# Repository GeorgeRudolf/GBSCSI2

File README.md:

# GBSCSI2
Affordable SCSI Disk Emulator - upgrade over the original GBSCSI

NOTE: Above all, these boards were initially designed as a hack to satisfy my own personal needs. With that said, they've been tested fairly extensively. Please read this entire README.

Herein are the design files for all variants of GBSCSI2 in KiCad 7 format, being migrated to KiCad 9. The hardware in this repository is licensed CERN OHL-S V2, the full terms of which can be found at https://ohwr.org/cern_ohl_s_v2.pdf and https://ohwr.org/cern_ohl_s_v2.txt.

With thanks to [The Decromancer](https://decromancer.ca/) for sponsoring this project; wohali, tr0n, compu85, sabur and luigi30 for testing; and the rest of UHF for their continued enthusiasm and support. Also to [Rabbit Hole Computing](https://www.rabbitholecomputing.com/) for their continued maintenance of the ZuluSCSI firmware that makes these boards complete, and further testing and collaboration on this project.

# HOW TO:
1. Buy board from decromancer or [Emmy Bear Retro](https://retro.emmybear.shop)
2. It arrives at your doorstep ready to use

OR

1. Get assembled boards using the files in this repository
2. Solder header of your choice
3. (Except for RP2040 version, or if ordering Pico from JLC) Solder RPi Pico - use Pico-W if you want DaynaPORT capabilities for a Mac
4. Go to https://github.com/ZuluSCSI/ZuluSCSI-firmware and grab the Pico/Pico_DaynaPORT version of the latest release and flash to the board by connecting via USB while holding BOOTSEL (or toggling the boot dip switch for RP2040)

# The (very important) details:

1. GBSCSI2 is being moved to a revised hierarchical design that allows for modularity and ease of customization, while maintaining uniformity. The whole project is considered WIP - this warning will be removed once things are tested. Previous versions have been moved to an archive folder. More about them below.

2. The archived Wide SCSI variants are BROKEN. They're incomplete and not usable. 
Rabbit Hole Computing has forked these designs, corrected their flaws and finished the implementation in a manner compatible with standard ZuluSCSI firmware. This fork is now available at https://github.com/ZuluSCSI/ZuluSCSI-Ultra-Wide-OSHW-RP2350B.

3. The variants tagged "untested" are exactly that. I've never personally made boards from them. Use at your own risk.

4. For changes and errata, see the relevant files in the repo.

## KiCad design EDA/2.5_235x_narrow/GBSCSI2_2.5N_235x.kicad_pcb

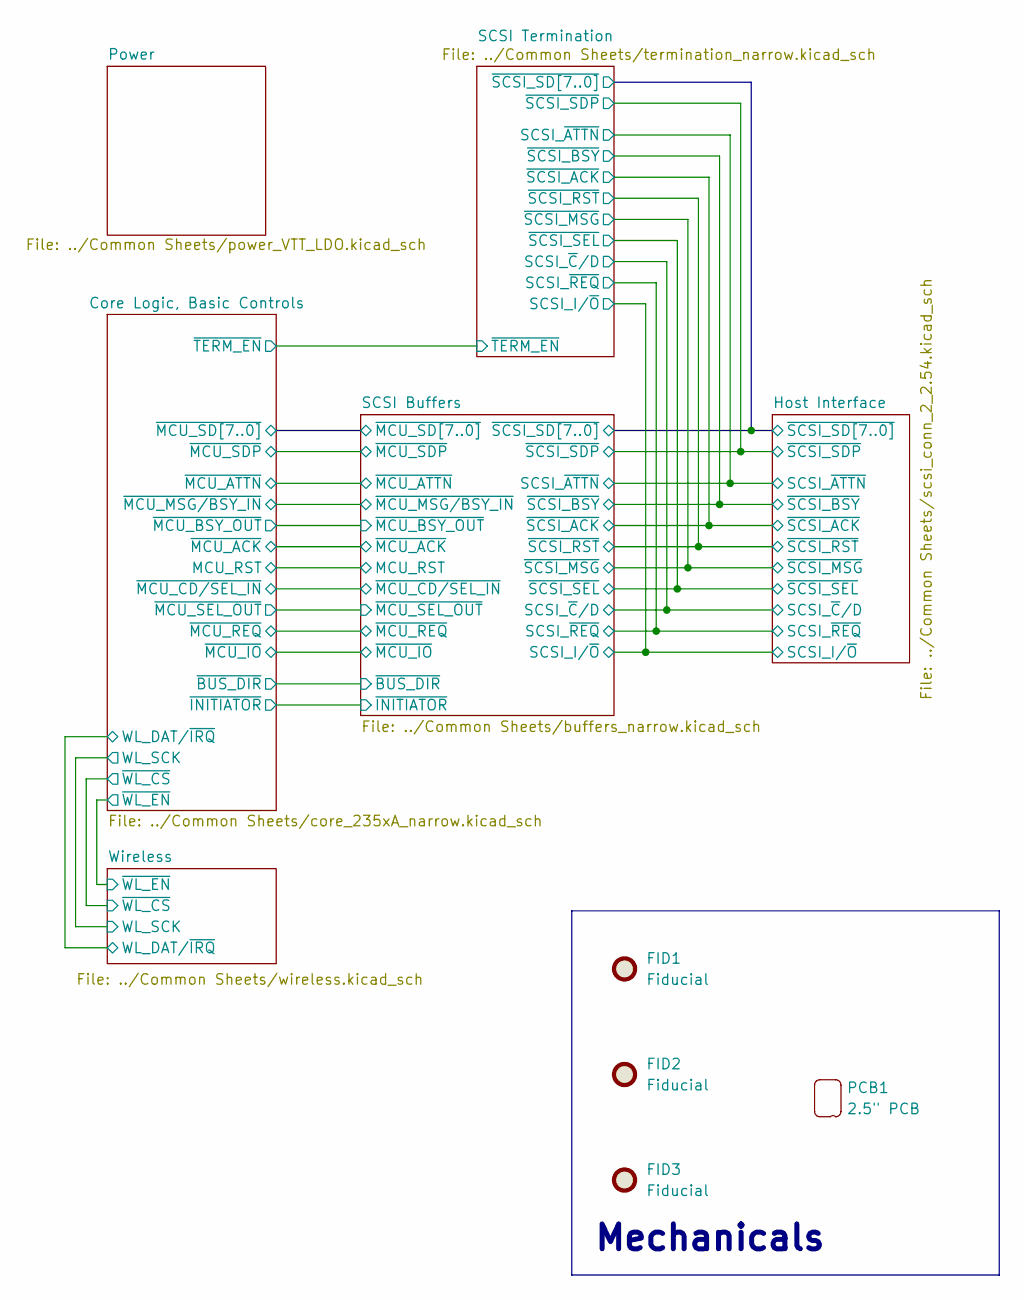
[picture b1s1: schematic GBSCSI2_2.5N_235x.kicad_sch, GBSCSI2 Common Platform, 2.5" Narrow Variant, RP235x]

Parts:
FID1, FID2, FID3: Fiducial; Fiducial_0.5mm_Mask1mm; LCSC N/A
PCB1: 2.5" PCB; GBSCSI2_2.5_PCB

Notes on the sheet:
Mechanicals

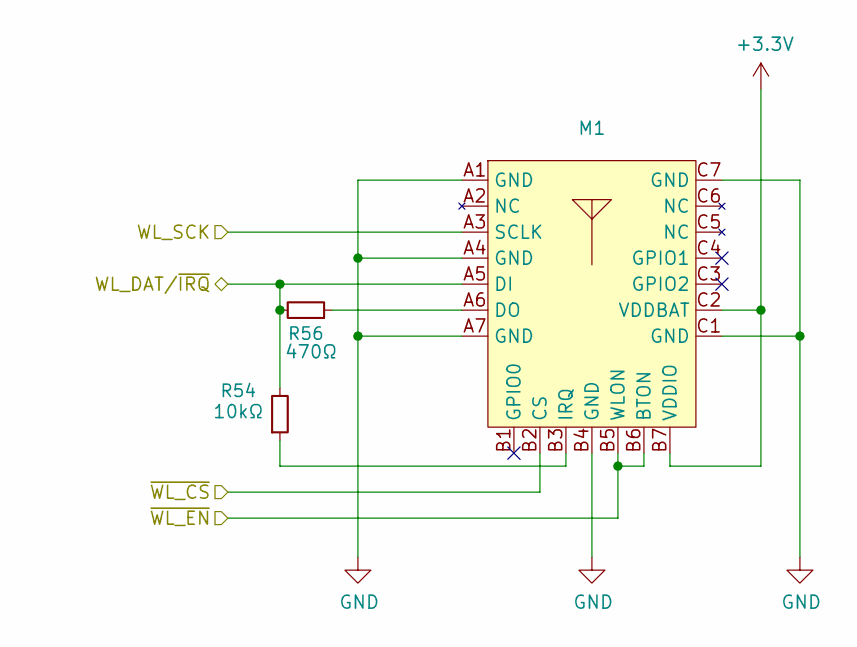
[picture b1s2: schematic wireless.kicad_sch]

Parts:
M1: RPi_RM2; LCSC N/A
R54: 10kΩ; R_0402_1005Metric; LCSC C25744
R56: 470Ω; R_0402_1005Metric

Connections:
+3.3V: M1.B7 (VDDIO), M1.C2 (VDDBAT); also elsewhere on the board
/Core Logic, Basic Controls/WL_DAT/~IRQ: M1.A5 (DI), R54.2, R56.2; also elsewhere on the board
/Core Logic, Basic Controls/WL_SCK: M1.A3 (SCLK); also elsewhere on the board
/Core Logic, Basic Controls/~WL_CS: M1.B2 (CS); also elsewhere on the board
/Core Logic, Basic Controls/~WL_EN: M1.B5 (WLON), M1.B6 (BTON); also elsewhere on the board
GND: M1.A1 (GND), M1.A4 (GND), M1.A7 (GND), M1.B4 (GND), M1.C1 (GND), M1.C7 (GND); also elsewhere on the board
unnamed: M1.A6 (DO), R56.1
unnamed: M1.B3 (IRQ), R54.1

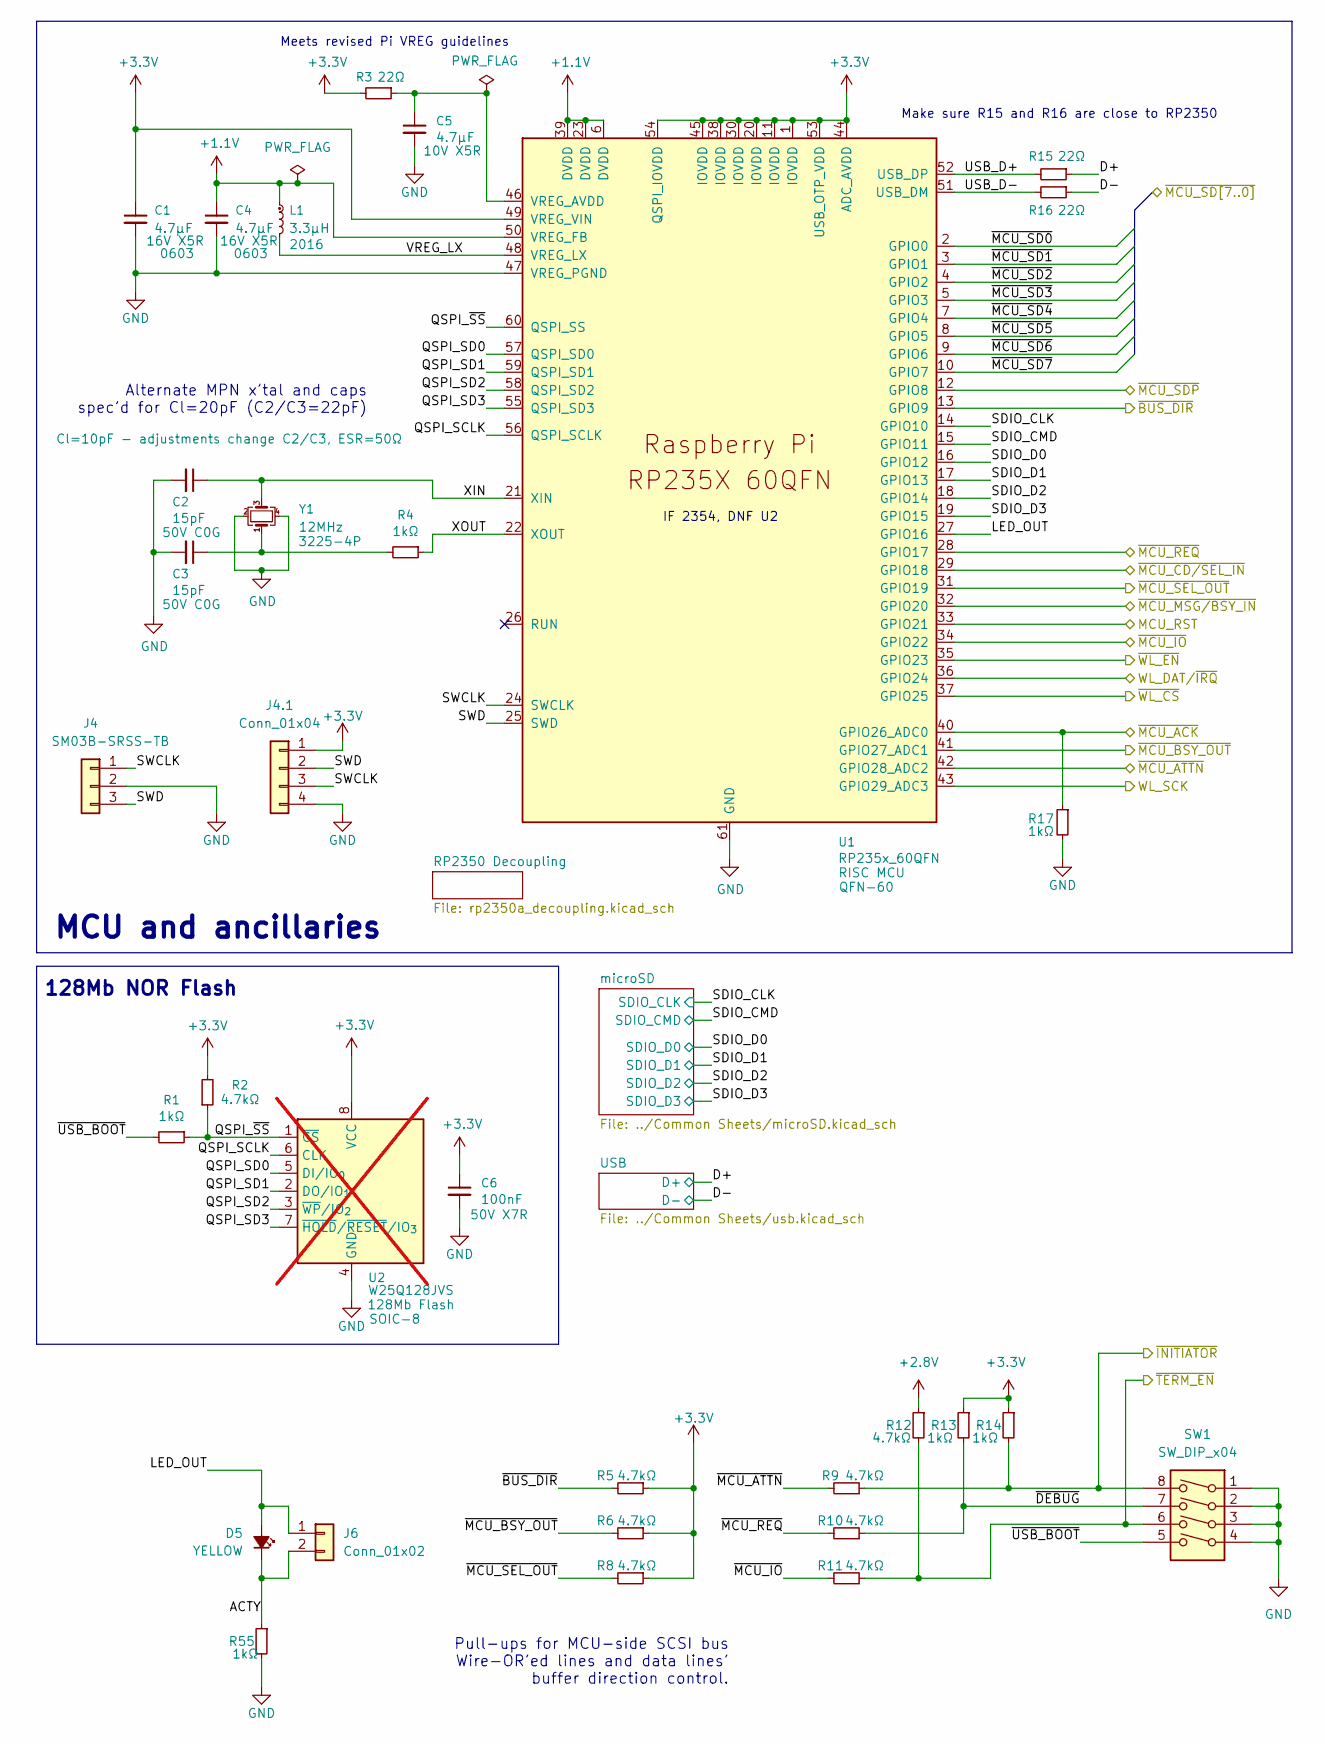
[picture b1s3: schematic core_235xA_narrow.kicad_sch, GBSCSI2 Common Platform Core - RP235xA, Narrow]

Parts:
C1, C4: 4.7μF; C_0603_1608Metric; LCSC C19666
C2, C3: 15pF; C_0402_1005Metric; LCSC C1548
C5: 4.7μF; C_0402_1005Metric; LCSC C23733
C6: 100nF; C_0402_1005Metric; LCSC C307331
D5: YELLOW; LED_0603_1608Metric; LCSC C72038
J4: SM03B-SRSS-TB; JST_SH_SM03B-SRSS-TB_1x03-1MP_P1.00mm_Horizontal; LCSC C160403
J4.1: Conn_01x04; PinHeader_1x04_P2.54mm_Vertical; LCSC N/A
J6: Conn_01x02; PinHeader_1x02_P2.54mm_Vertical; LCSC N/A
L1: 3.3μH; L_Abracon_AOTA-B2016; LCSC C42411119
R1, R4: 1kΩ; R_0402_1005Metric; LCSC C11702
R2: 4.7kΩ; R_0402_1005Metric; LCSC C25900
R3, R15, R16: 22Ω; R_0402_1005Metric; LCSC C25092
R5, R6, R8, R9, R10, R11, R12: 4.7kΩ; R_0603_1608Metric; LCSC C23162
R13, R14, R17, R55: 1kΩ; R_0603_1608Metric; LCSC C21190
SW1: SW_DIP_x04; SW_DIP_SPSTx04_Slide_6.7x11.72mm_W8.61mm_P2.54mm_LowProfile; LCSC C5160841
U1: RP235x_60QFN; RP2350-QFN-60-1EP_7x7_P0.4mm_EP3.4x3.4mm_ThermalVias; LCSC C41378174
U2: W25Q128JVS; SOIC-8_5.3x5.3mm_P1.27mm; LCSC C97521; not fitted
Y1: 12MHz; Crystal_SMD_3225-4Pin_3.2x2.5mm; LCSC C20625731

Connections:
+1.1V: C4.1, L1.1, U1.6 (DVDD), U1.23 (DVDD), U1.39 (DVDD), U1.50 (VREG_FB); also elsewhere on the board
+2.8V: R12.1; also elsewhere on the board
+3.3V: C1.1, C6.1, J4.1.1, R2.2, R3.2, R5.1, R6.1, R8.1, R13.1, R14.1, U1.1 (IOVDD), U1.11 (IOVDD), U1.20 (IOVDD), U1.30 (IOVDD), U1.38 (IOVDD), U1.44 (ADC_AVDD), U1.45 (IOVDD), U1.49 (VREG_VIN), U1.53 (USB_OTP_VDD), U1.54 (QSPI_IOVDD), U2.8 (VCC); also elsewhere on the board
/Core Logic, Basic Controls/ACTY: D5.1 (K), J6.2, R55.1
/Core Logic, Basic Controls/D+: R15.1; also elsewhere on the board
/Core Logic, Basic Controls/D-: R16.1; also elsewhere on the board
/Core Logic, Basic Controls/LED_OUT: D5.2 (A), J6.1, U1.27 (GPIO16)
/Core Logic, Basic Controls/MCU_RST: U1.33 (GPIO21); also elsewhere on the board
/Core Logic, Basic Controls/QSPI_SCLK: U1.56 (QSPI_SCLK), U2.6 (CLK)
/Core Logic, Basic Controls/QSPI_SD0: U1.57 (QSPI_SD0), U2.5 (DI/IO_{0})
/Core Logic, Basic Controls/QSPI_SD1: U1.59 (QSPI_SD1), U2.2 (DO/IO_{1})
/Core Logic, Basic Controls/QSPI_SD2: U1.58 (QSPI_SD2), U2.3 (~WP/IO_{2})
/Core Logic, Basic Controls/QSPI_SD3: U1.55 (QSPI_SD3), U2.7 (~HOLD/~RESET/IO_{3})
/Core Logic, Basic Controls/QSPI_~SS: R1.1, R2.1, U1.60 (QSPI_SS), U2.1 (~CS)
/Core Logic, Basic Controls/SDIO_CLK: U1.14 (GPIO10); also elsewhere on the board
/Core Logic, Basic Controls/SDIO_CMD: U1.15 (GPIO11); also elsewhere on the board
/Core Logic, Basic Controls/SDIO_D0: U1.16 (GPIO12); also elsewhere on the board
/Core Logic, Basic Controls/SDIO_D1: U1.17 (GPIO13); also elsewhere on the board
/Core Logic, Basic Controls/SDIO_D2: U1.18 (GPIO14); also elsewhere on the board
/Core Logic, Basic Controls/SDIO_D3: U1.19 (GPIO15); also elsewhere on the board
/Core Logic, Basic Controls/SWCLK: J4.1, J4.1.3, U1.24 (SWCLK)
/Core Logic, Basic Controls/SWD: J4.3, J4.1.2, U1.25 (SWD)
/Core Logic, Basic Controls/USB_D+: R15.2, U1.52 (USB_DP)
/Core Logic, Basic Controls/USB_D-: R16.2, U1.51 (USB_DM)
/Core Logic, Basic Controls/VREG_LX: L1.2, U1.48 (VREG_LX)
/Core Logic, Basic Controls/WL_DAT/~IRQ: U1.36 (GPIO24); also elsewhere on the board
/Core Logic, Basic Controls/WL_SCK: U1.43 (GPIO29_ADC3); also elsewhere on the board
/Core Logic, Basic Controls/XIN: C2.1, U1.21 (XIN), Y1.3
/Core Logic, Basic Controls/XOUT: R4.1, U1.22 (XOUT)
/Core Logic, Basic Controls/~BUS_DIR: R5.2, U1.13 (GPIO9); also elsewhere on the board
/Core Logic, Basic Controls/~DEBUG: R10.1, R13.2, SW1.7
/Core Logic, Basic Controls/~INITIATOR: R9.1, R14.2, SW1.8; also elsewhere on the board
/Core Logic, Basic Controls/~MCU_ACK: R17.1, U1.40 (GPIO26_ADC0); also elsewhere on the board
/Core Logic, Basic Controls/~MCU_ATTN: R9.2, U1.42 (GPIO28_ADC2); also elsewhere on the board
/Core Logic, Basic Controls/~MCU_BSY_OUT: R6.2, U1.41 (GPIO27_ADC1); also elsewhere on the board
/Core Logic, Basic Controls/~MCU_CD/SEL_IN: U1.29 (GPIO18); also elsewhere on the board
/Core Logic, Basic Controls/~MCU_IO: R11.2, U1.34 (GPIO22); also elsewhere on the board
/Core Logic, Basic Controls/~MCU_MSG/BSY_IN: U1.32 (GPIO20); also elsewhere on the board
/Core Logic, Basic Controls/~MCU_REQ: R10.2, U1.28 (GPIO17); also elsewhere on the board
/Core Logic, Basic Controls/~MCU_SD0: U1.2 (GPIO0); also elsewhere on the board
/Core Logic, Basic Controls/~MCU_SD1: U1.3 (GPIO1); also elsewhere on the board
/Core Logic, Basic Controls/~MCU_SD2: U1.4 (GPIO2); also elsewhere on the board
/Core Logic, Basic Controls/~MCU_SD3: U1.5 (GPIO3); also elsewhere on the board
/Core Logic, Basic Controls/~MCU_SD4: U1.7 (GPIO4); also elsewhere on the board
/Core Logic, Basic Controls/~MCU_SD5: U1.8 (GPIO5); also elsewhere on the board
/Core Logic, Basic Controls/~MCU_SD6: U1.9 (GPIO6); also elsewhere on the board
/Core Logic, Basic Controls/~MCU_SD7: U1.10 (GPIO7); also elsewhere on the board
/Core Logic, Basic Controls/~MCU_SDP: U1.12 (GPIO8); also elsewhere on the board
/Core Logic, Basic Controls/~MCU_SEL_OUT: R8.2, U1.31 (GPIO19); also elsewhere on the board
/Core Logic, Basic Controls/~TERM_EN: R11.1, R12.2, SW1.6; also elsewhere on the board
/Core Logic, Basic Controls/~USB_BOOT: R1.2, SW1.5
/Core Logic, Basic Controls/~WL_CS: U1.37 (GPIO25); also elsewhere on the board
/Core Logic, Basic Controls/~WL_EN: U1.35 (GPIO23); also elsewhere on the board
GND: C1.2, C2.2, C3.2, C4.2, C5.2, C6.2, J4.2, J4.1.4, R17.2, R55.2, SW1.1, SW1.2, SW1.3, SW1.4, U1.47 (VREG_PGND), U1.61 (GND), U2.4 (GND), Y1.2, Y1.4; also elsewhere on the board
unnamed: C3.1, R4.2, Y1.1
unnamed: C5.1, R3.1, U1.46 (VREG_AVDD)

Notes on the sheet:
128Mb NOR Flash
Alternate MPN x'tal and caps spec'd for Cl=20pF (C2/C3=22pF)
Pull-ups for MCU-side SCSI bus Wire-OR'ed lines and data lines' buffer direction control.
IF 2354, DNF U2
MCU and ancillaries
Make sure R15 and R16 are close to RP2350
Meets revised Pi VREG guidelines

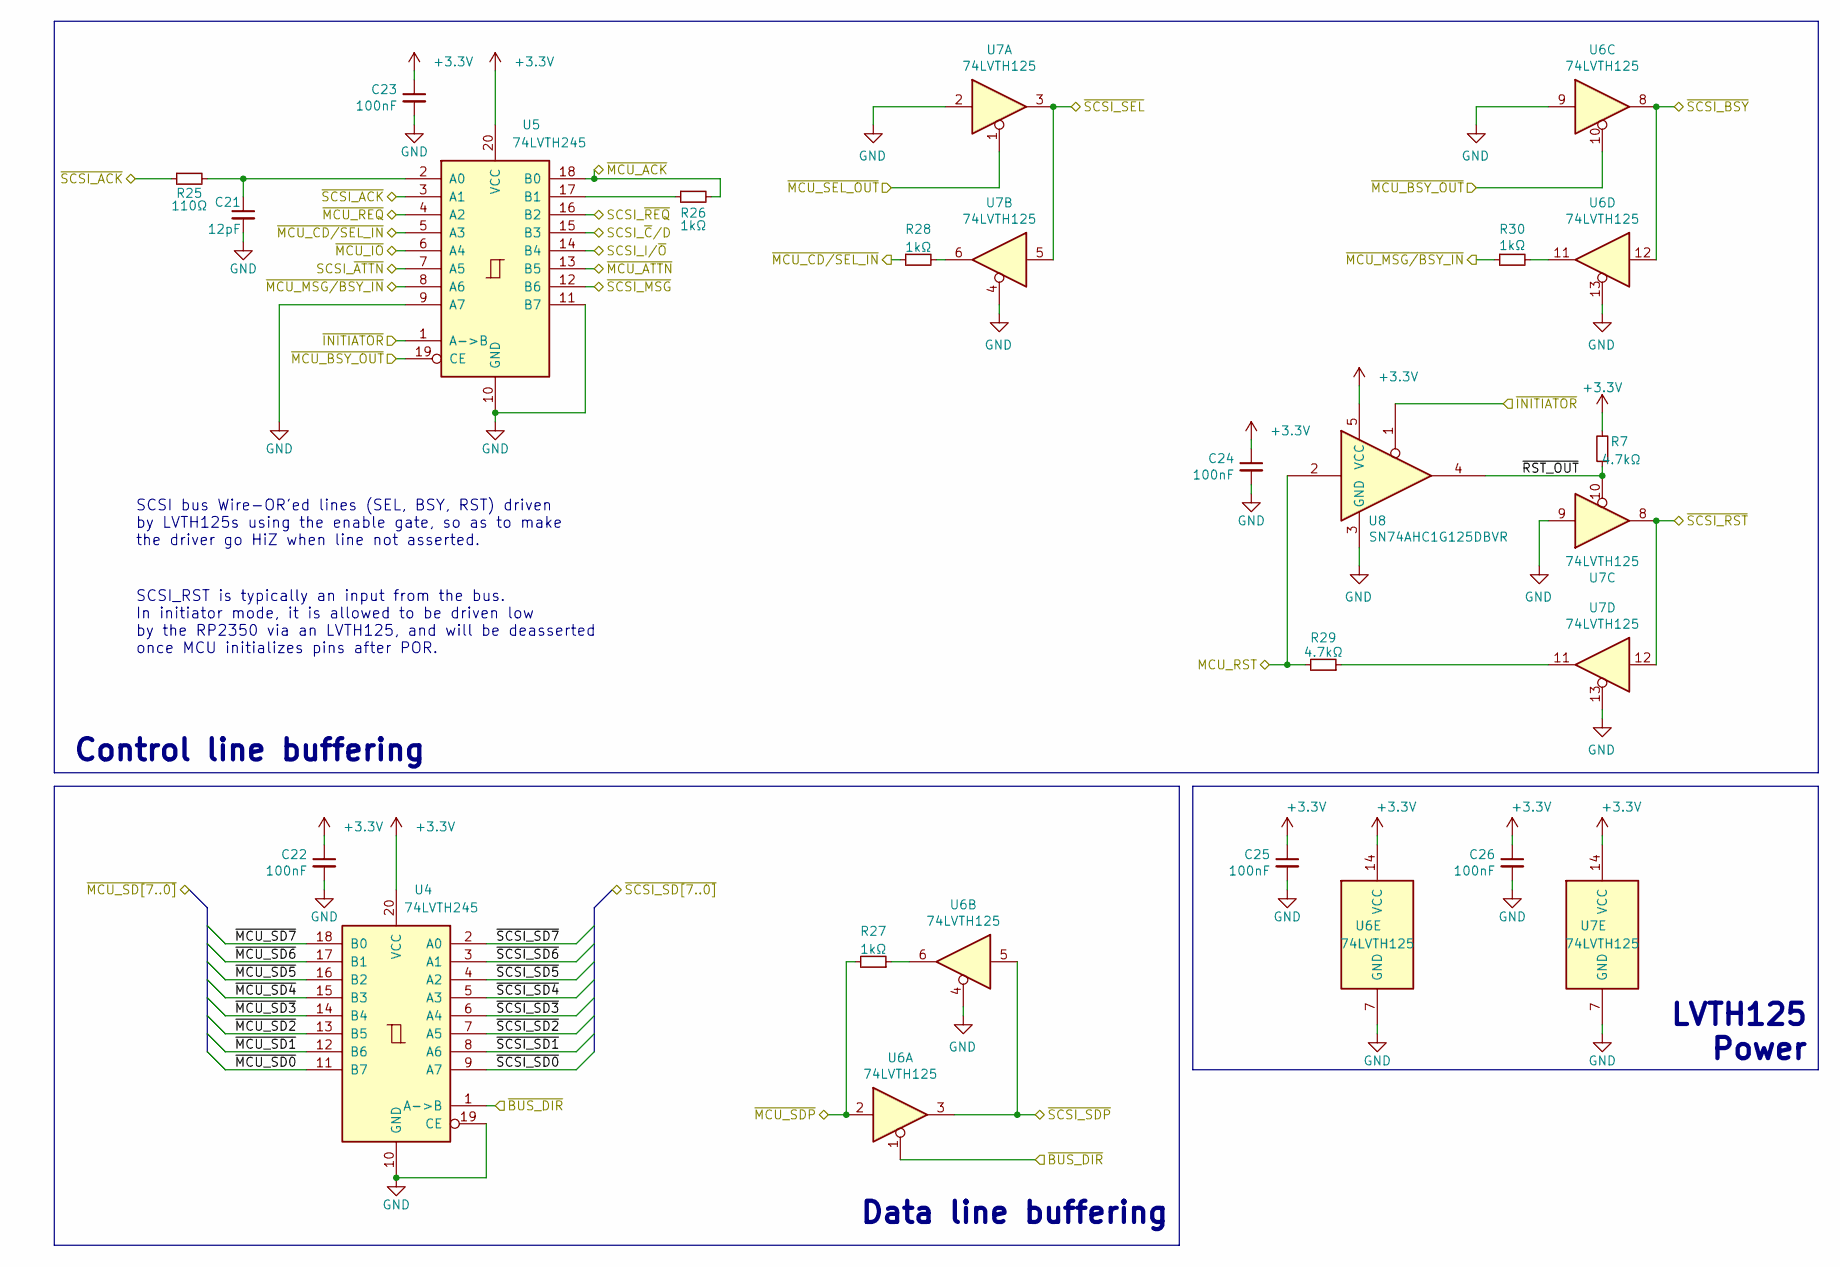
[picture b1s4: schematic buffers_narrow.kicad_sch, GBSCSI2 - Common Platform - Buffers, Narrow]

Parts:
C21: 12pF; C_0603_1608Metric; LCSC C38523
C22, C23, C24, C25, C26: 100nF; C_0603_1608Metric; LCSC C14663
R7, R29: 4.7kΩ; R_0603_1608Metric; LCSC C23162
R25: 110Ω; R_0603_1608Metric; LCSC C22781
R26, R27, R28, R30: 1kΩ; R_0603_1608Metric; LCSC C21190
U4, U5: 74LVTH245; SSOP-20_5.3x7.2mm_P0.65mm; LCSC C2652121
U6, U7: 74LVTH125; TSSOP-14_4.4x5mm_P0.65mm; LCSC C7042
U8: SN74AHC1G125DBVR; SOT-23-5; LCSC C7468

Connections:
+3.3V: C22.1, C23.1, C24.1, C25.1, C26.1, R7.2, U4.20 (VCC), U5.20 (VCC), U6.14 (VCC), U7.14 (VCC), U8.5 (VCC); also elsewhere on the board
/Core Logic, Basic Controls/MCU_RST: R29.2, U8.2; also elsewhere on the board
/Core Logic, Basic Controls/~BUS_DIR: U4.1 (A->B), U6.1; also elsewhere on the board
/Core Logic, Basic Controls/~INITIATOR: U5.1 (A->B), U8.1; also elsewhere on the board
/Core Logic, Basic Controls/~MCU_ACK: R26.2, U5.18 (B0); also elsewhere on the board
/Core Logic, Basic Controls/~MCU_ATTN: U5.13 (B5); also elsewhere on the board
/Core Logic, Basic Controls/~MCU_BSY_OUT: U5.19 (CE), U6.10; also elsewhere on the board
/Core Logic, Basic Controls/~MCU_CD/SEL_IN: R28.1, U5.5 (A3); also elsewhere on the board
/Core Logic, Basic Controls/~MCU_IO: U5.6 (A4); also elsewhere on the board
/Core Logic, Basic Controls/~MCU_MSG/BSY_IN: R30.1, U5.8 (A6); also elsewhere on the board
/Core Logic, Basic Controls/~MCU_REQ: U5.4 (A2); also elsewhere on the board
/Core Logic, Basic Controls/~MCU_SD0: U4.11 (B7); also elsewhere on the board
/Core Logic, Basic Controls/~MCU_SD1: U4.12 (B6); also elsewhere on the board
/Core Logic, Basic Controls/~MCU_SD2: U4.13 (B5); also elsewhere on the board
/Core Logic, Basic Controls/~MCU_SD3: U4.14 (B4); also elsewhere on the board
/Core Logic, Basic Controls/~MCU_SD4: U4.15 (B3); also elsewhere on the board
/Core Logic, Basic Controls/~MCU_SD5: U4.16 (B2); also elsewhere on the board
/Core Logic, Basic Controls/~MCU_SD6: U4.17 (B1); also elsewhere on the board
/Core Logic, Basic Controls/~MCU_SD7: U4.18 (B0); also elsewhere on the board
/Core Logic, Basic Controls/~MCU_SDP: R27.2, U6.2; also elsewhere on the board
/Core Logic, Basic Controls/~MCU_SEL_OUT: U7.1; also elsewhere on the board
/Host Interface/SCSI_I/~O: U5.14 (B4); also elsewhere on the board
/Host Interface/SCSI_~ATTN: U5.7 (A5); also elsewhere on the board
/Host Interface/SCSI_~C/D: U5.15 (B3); also elsewhere on the board
/Host Interface/SCSI_~REQ: U5.16 (B2); also elsewhere on the board
/Host Interface/~SCSI_ACK: R25.1, U5.3 (A1); also elsewhere on the board
/Host Interface/~SCSI_BSY: U6.8, U6.12; also elsewhere on the board
/Host Interface/~SCSI_MSG: U5.12 (B6); also elsewhere on the board
/Host Interface/~SCSI_RST: U7.8, U7.12; also elsewhere on the board
/Host Interface/~SCSI_SD0: U4.9 (A7); also elsewhere on the board
/Host Interface/~SCSI_SD1: U4.8 (A6); also elsewhere on the board
/Host Interface/~SCSI_SD2: U4.7 (A5); also elsewhere on the board
/Host Interface/~SCSI_SD3: U4.6 (A4); also elsewhere on the board
/Host Interface/~SCSI_SD4: U4.5 (A3); also elsewhere on the board
/Host Interface/~SCSI_SD5: U4.4 (A2); also elsewhere on the board
/Host Interface/~SCSI_SD6: U4.3 (A1); also elsewhere on the board
/Host Interface/~SCSI_SD7: U4.2 (A0); also elsewhere on the board
/Host Interface/~SCSI_SDP: U6.3, U6.5; also elsewhere on the board
/Host Interface/~SCSI_SEL: U7.3, U7.5; also elsewhere on the board
/SCSI Buffers/~RST_OUT: R7.1, U7.10, U8.4
GND: C21.2, C22.2, C23.2, C24.2, C25.2, C26.2, U4.10 (GND), U4.19 (CE), U5.9 (A7), U5.10 (GND), U5.11 (B7), U6.4, U6.7 (GND), U6.9, U6.13, U7.2, U7.4, U7.7 (GND), U7.9, U7.13, U8.3 (GND); also elsewhere on the board
unnamed: R27.1, U6.6
unnamed: R28.2, U7.6
unnamed: R29.1, U7.11
unnamed: R30.2, U6.11
unnamed: C21.1, R25.2, U5.2 (A0)
unnamed: R26.1, U5.17 (B1)

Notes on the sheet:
Control line buffering
SCSI_RST is typically an input from the bus. In initiator mode, it is allowed to be driven low by the RP2350 via an LVTH125, and will be deasserted once MCU initializes pins after POR.
LVTH125 Power
SCSI bus Wire-OR'ed lines (SEL, BSY, RST) driven by LVTH125s using the enable gate, so as to make the driver go HiZ when line not asserted.
Data line buffering

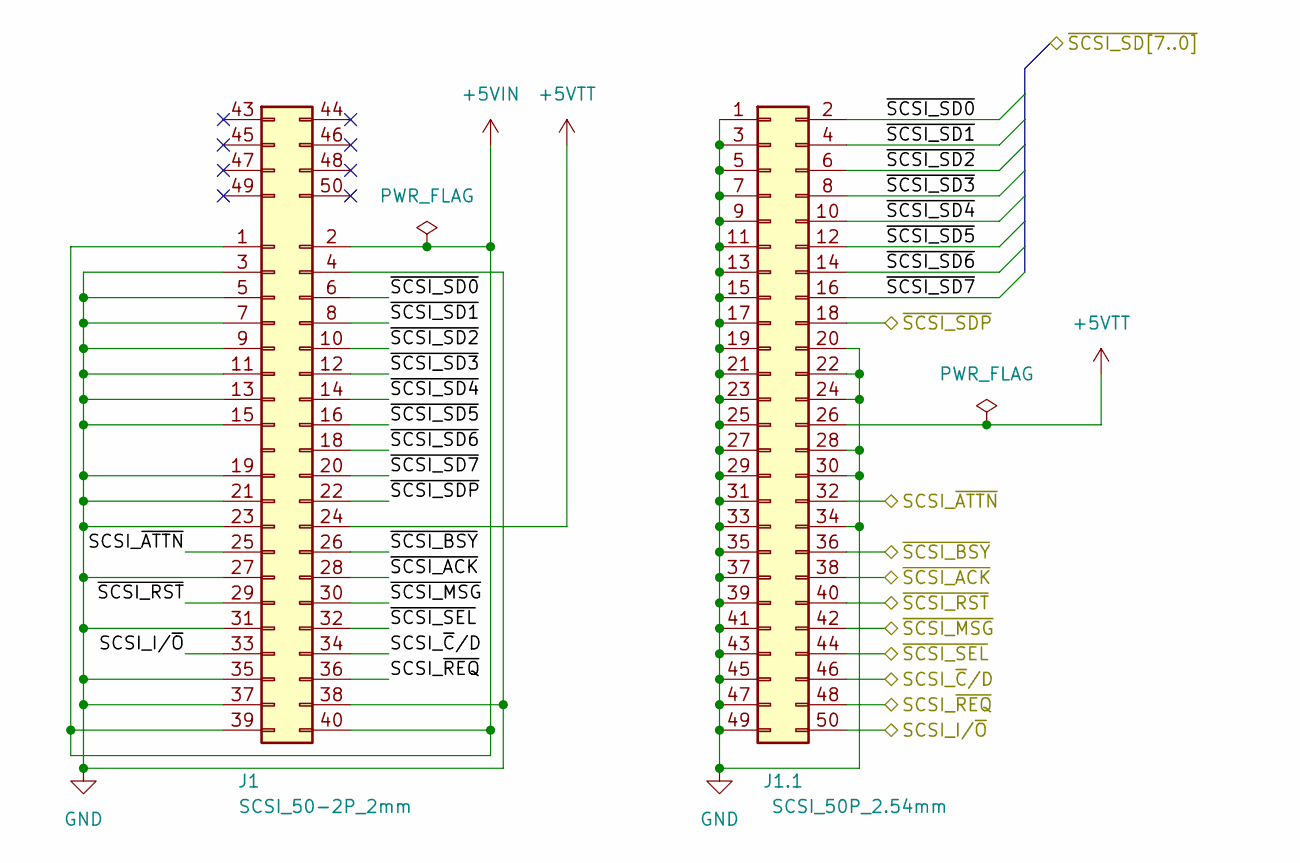
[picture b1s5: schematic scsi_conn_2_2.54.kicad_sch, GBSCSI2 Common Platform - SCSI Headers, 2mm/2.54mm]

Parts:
J1: SCSI_50-2P_2mm; PinHeader_2x25-2_P2.00mm_straddle; LCSC N/A
J1.1: SCSI_50P_2.54mm; IDC-Header_2x25_P2.54mm_Horizontal; LCSC N/A

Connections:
+5VIN: J1.1, J1.2, J1.39, J1.40; also elsewhere on the board
+5VTT: J1.24, J1.1.26; also elsewhere on the board
/Host Interface/SCSI_I/~O: J1.33, J1.1.50; also elsewhere on the board
/Host Interface/SCSI_~ATTN: J1.25, J1.1.32; also elsewhere on the board
/Host Interface/SCSI_~C/D: J1.34, J1.1.46; also elsewhere on the board
/Host Interface/SCSI_~REQ: J1.36, J1.1.48; also elsewhere on the board
/Host Interface/~SCSI_ACK: J1.28, J1.1.38; also elsewhere on the board
/Host Interface/~SCSI_BSY: J1.26, J1.1.36; also elsewhere on the board
/Host Interface/~SCSI_MSG: J1.30, J1.1.42; also elsewhere on the board
/Host Interface/~SCSI_RST: J1.29, J1.1.40; also elsewhere on the board
/Host Interface/~SCSI_SD0: J1.6, J1.1.2; also elsewhere on the board
/Host Interface/~SCSI_SD1: J1.8, J1.1.4; also elsewhere on the board
/Host Interface/~SCSI_SD2: J1.10, J1.1.6; also elsewhere on the board
/Host Interface/~SCSI_SD3: J1.12, J1.1.8; also elsewhere on the board
/Host Interface/~SCSI_SD4: J1.14, J1.1.10; also elsewhere on the board
/Host Interface/~SCSI_SD5: J1.16, J1.1.12; also elsewhere on the board
/Host Interface/~SCSI_SD6: J1.18, J1.1.14; also elsewhere on the board
/Host Interface/~SCSI_SD7: J1.20, J1.1.16; also elsewhere on the board
/Host Interface/~SCSI_SDP: J1.22, J1.1.18; also elsewhere on the board
/Host Interface/~SCSI_SEL: J1.32, J1.1.44; also elsewhere on the board
GND: J1.3, J1.4, J1.5, J1.7, J1.9, J1.11, J1.13, J1.15, J1.19, J1.21, J1.23, J1.27, J1.31, J1.35, J1.37, J1.38, J1.1.1, J1.1.3, J1.1.5, J1.1.7, J1.1.9, J1.1.11, J1.1.13, J1.1.15, J1.1.17, J1.1.19, J1.1.20, J1.1.21, J1.1.22, J1.1.23, J1.1.24, J1.1.25, J1.1.27, J1.1.28, J1.1.29, J1.1.30, J1.1.31, J1.1.33, J1.1.34, J1.1.35, J1.1.37, J1.1.39, J1.1.41, J1.1.43, J1.1.45, J1.1.47, J1.1.49; also elsewhere on the board

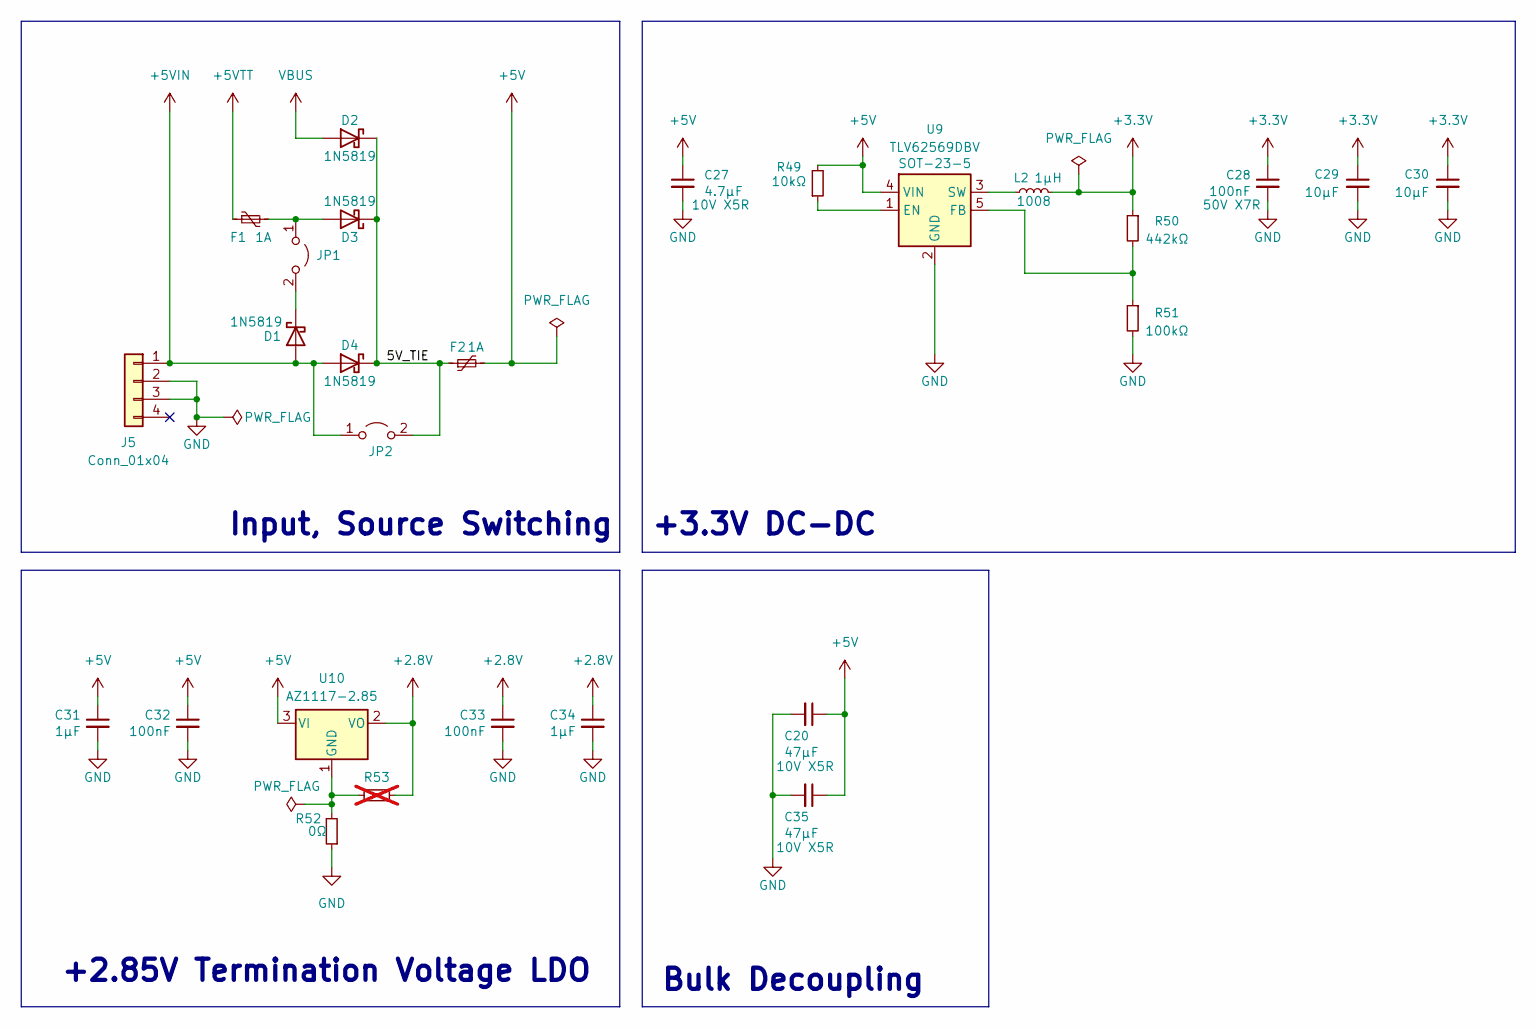
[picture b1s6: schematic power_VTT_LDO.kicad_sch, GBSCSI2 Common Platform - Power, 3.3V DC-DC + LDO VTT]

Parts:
C20, C35: 47μF; C_1206_3216Metric; LCSC C96123
C27: 4.7μF; C_0402_1005Metric; LCSC C23733
C28: 100nF; C_0402_1005Metric; LCSC C307331
C29, C30: 10μF; C_0603_1608Metric; LCSC C96446
C31, C34: 1μF; C_0603_1608Metric; LCSC C15849
C32, C33: 100nF; C_0603_1608Metric; LCSC C14663
D1, D2, D3, D4: 1N5819; D_SOD-123; LCSC C191023
F1, F2: 1A; Fuse_0805_2012Metric; LCSC C468888
J5: Conn_01x04; PinHeader_1x04_P2.54mm_Horizontal; LCSC N/A
JP1, JP2: Jumper_2_Open; PinHeader_2x01_P2.54mm_Vertical; LCSC N/A
L2: 1μH; L_1008_2520Metric; LCSC C5832356
R49: 10kΩ; R_0402_1005Metric; LCSC C25744
R50: 442kΩ; R_0402_1005Metric; LCSC C5101
R51: 100kΩ; R_0402_1005Metric; LCSC C25741
R52: 0Ω; R_0603_1608Metric; LCSC C21189
R53: R_0603_1608Metric; LCSC N/A; not fitted
U9: TLV62569DBV; SOT-23-5; LCSC C141836
U10: AZ1117-2.85; SOT-223-3_TabPin2; LCSC C14791

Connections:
+2.8V: C33.1, C34.1, R53.2, U10.2 (VO); also elsewhere on the board
+3.3V: C28.1, C29.1, C30.1, L2.2, R50.1; also elsewhere on the board
+5V: C20.1, C27.1, C31.1, C32.1, C35.1, F2.2, R49.2, U9.4 (VIN), U10.3 (VI)
+5VIN: D1.2 (A), D4.2 (A), J5.1, JP2.1 (A); also elsewhere on the board
+5VTT: F1.1; also elsewhere on the board
/Power/5V_TIE: D2.1 (K), D3.1 (K), D4.1 (K), F2.1, JP2.2 (B)
GND: C20.2, C27.2, C28.2, C29.2, C30.2, C31.2, C32.2, C33.2, C34.2, C35.2, J5.2, J5.3, R51.2, R52.1, U9.2 (GND); also elsewhere on the board
unnamed: D1.1 (K), JP1.2 (B)
unnamed: D3.2 (A), F1.2, JP1.1 (A)
unnamed: R49.1, U9.1 (EN)
unnamed: R50.2, R51.1, U9.5 (FB)
unnamed: L2.1, U9.3 (SW)
unnamed: R52.2, R53.1, U10.1 (GND)
VBUS: D2.2 (A); also elsewhere on the board

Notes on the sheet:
+2.85V Termination Voltage LDO
+3.3V DC-DC
Bulk Decoupling
Input, Source Switching

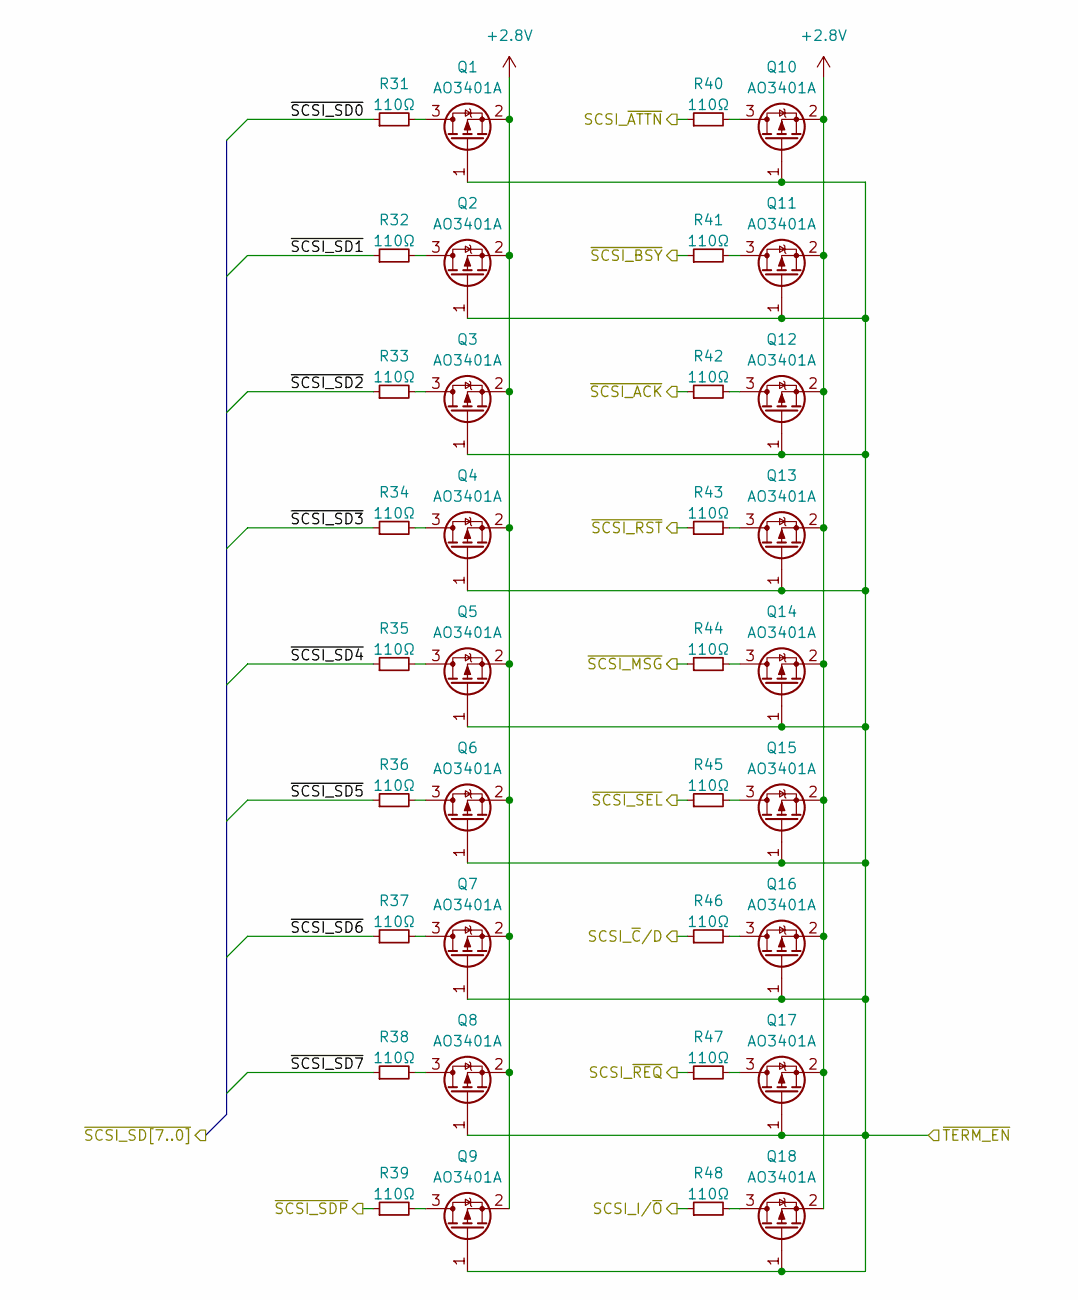
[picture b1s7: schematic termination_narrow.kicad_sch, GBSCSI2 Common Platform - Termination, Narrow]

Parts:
Q1, Q2, Q3, Q4, Q5, Q6, Q7, Q8, Q9, Q10, Q11, Q12, Q13, Q14, Q15, Q16, Q17, Q18: AO3401A; SOT-23; LCSC C15127
R31, R32, R33, R34, R35, R36, R37, R38, R39, R40, R41, R42, R43, R44, R45, R46, R47, R48: 110Ω; R_0603_1608Metric; LCSC C22781

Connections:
+2.8V: Q1.2 (S), Q2.2 (S), Q3.2 (S), Q4.2 (S), Q5.2 (S), Q6.2 (S), Q7.2 (S), Q8.2 (S), Q9.2 (S), Q10.2 (S), Q11.2 (S), Q12.2 (S), Q13.2 (S), Q14.2 (S), Q15.2 (S), Q16.2 (S), Q17.2 (S), Q18.2 (S); also elsewhere on the board
/Core Logic, Basic Controls/~TERM_EN: Q1.1 (G), Q2.1 (G), Q3.1 (G), Q4.1 (G), Q5.1 (G), Q6.1 (G), Q7.1 (G), Q8.1 (G), Q9.1 (G), Q10.1 (G), Q11.1 (G), Q12.1 (G), Q13.1 (G), Q14.1 (G), Q15.1 (G), Q16.1 (G), Q17.1 (G), Q18.1 (G); also elsewhere on the board
/Host Interface/SCSI_I/~O: R48.1; also elsewhere on the board
/Host Interface/SCSI_~ATTN: R40.1; also elsewhere on the board
/Host Interface/SCSI_~C/D: R46.1; also elsewhere on the board
/Host Interface/SCSI_~REQ: R47.1; also elsewhere on the board
/Host Interface/~SCSI_ACK: R42.1; also elsewhere on the board
/Host Interface/~SCSI_BSY: R41.1; also elsewhere on the board
/Host Interface/~SCSI_MSG: R44.1; also elsewhere on the board
/Host Interface/~SCSI_RST: R43.1; also elsewhere on the board
/Host Interface/~SCSI_SD0: R31.1; also elsewhere on the board
/Host Interface/~SCSI_SD1: R32.1; also elsewhere on the board
/Host Interface/~SCSI_SD2: R33.1; also elsewhere on the board
/Host Interface/~SCSI_SD3: R34.1; also elsewhere on the board
/Host Interface/~SCSI_SD4: R35.1; also elsewhere on the board
/Host Interface/~SCSI_SD5: R36.1; also elsewhere on the board
/Host Interface/~SCSI_SD6: R37.1; also elsewhere on the board
/Host Interface/~SCSI_SD7: R38.1; also elsewhere on the board
/Host Interface/~SCSI_SDP: R39.1; also elsewhere on the board
/Host Interface/~SCSI_SEL: R45.1; also elsewhere on the board
unnamed: Q1.3 (D), R31.2
unnamed: Q2.3 (D), R32.2
unnamed: Q3.3 (D), R33.2
unnamed: Q4.3 (D), R34.2
unnamed: Q5.3 (D), R35.2
unnamed: Q6.3 (D), R36.2
unnamed: Q7.3 (D), R37.2
unnamed: Q8.3 (D), R38.2
unnamed: Q9.3 (D), R39.2
unnamed: Q10.3 (D), R40.2
unnamed: Q11.3 (D), R41.2
unnamed: Q12.3 (D), R42.2
unnamed: Q13.3 (D), R43.2
unnamed: Q14.3 (D), R44.2
unnamed: Q15.3 (D), R45.2
unnamed: Q16.3 (D), R46.2
unnamed: Q17.3 (D), R47.2
unnamed: Q18.3 (D), R48.2

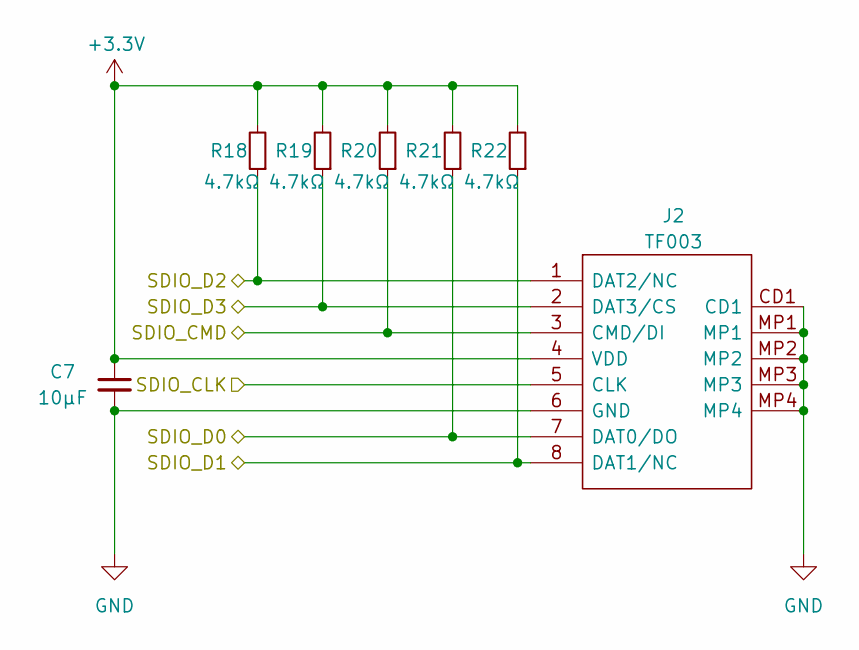
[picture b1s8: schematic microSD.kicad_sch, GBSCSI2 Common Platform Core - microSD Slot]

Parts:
C7: 10μF; C_0603_1608Metric; LCSC C96446
J2: TF003; TF01A; LCSC C5155563
R18, R19, R20, R21, R22: 4.7kΩ; R_0603_1608Metric; LCSC C23162

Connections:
+3.3V: C7.1, J2.4 (VDD), R18.2, R19.2, R20.2, R21.2, R22.2; also elsewhere on the board
/Core Logic, Basic Controls/SDIO_CLK: J2.5 (CLK); also elsewhere on the board
/Core Logic, Basic Controls/SDIO_CMD: J2.3 (CMD/DI), R20.1; also elsewhere on the board
/Core Logic, Basic Controls/SDIO_D0: J2.7 (DAT0/DO), R21.1; also elsewhere on the board
/Core Logic, Basic Controls/SDIO_D1: J2.8 (DAT1/NC), R22.1; also elsewhere on the board
/Core Logic, Basic Controls/SDIO_D2: J2.1 (DAT2/NC), R18.1; also elsewhere on the board
/Core Logic, Basic Controls/SDIO_D3: J2.2 (DAT3/CS), R19.1; also elsewhere on the board
GND: C7.2, J2.6 (GND), J2.CD1, J2.MP1, J2.MP2, J2.MP3, J2.MP4; also elsewhere on the board

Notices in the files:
EDA/2.5_235x_narrow/GBSCSI2_2.5N_235x.kicad_pcb:
artwork © grm, 2026
OSHW CERN OHL-S V2
rp2350_2.5_3.5_narrow/gbscsi2.kicad_pcb:
(c)2024, 2025 grm
rp2350_SCA_2.5/gbscsi2.kicad_pcb:
artwork © grm, 2025 github.com/GeorgeRudolf/GBSCSI2
